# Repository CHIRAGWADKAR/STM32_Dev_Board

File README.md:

# STM32 PCB Design Project

## STM32F103C8T6 Dev Board (Custom PCB)

This repository contains the complete KiCad project files for a custom development board based on the **STM32F103C8T6** microcontroller, 
commonly used in embedded systems and ARM Cortex-M3 learning platforms.

Designed by: **Chirag Wadkar**  
Toolchain: **KiCad 5.1.15**

---

## 🔧 Features & Specifications

- **Microcontroller**: STM32F103C8T6 (ARM Cortex-M3, 72 MHz, 64 KB Flash, 20 KB RAM)
- **Voltage Regulation**: AMS1117-3.3 LDO with LED power indicator
- **Power Supply**: USB Micro-B (VBus) → 3.3V regulated
- **External Oscillator**:
  - 16 MHz crystal connected to PD0 (HSE_IN) & PD1 (HSE_OUT)
- **USB Interface**:
  - USB Micro-B connected to PA11 (D-) and PA12 (D+)
  - 1.5kΩ pull-up resistor on D+
- **Communication**:
  - UART: PB6 (TX), PB7 (RX)
  - I2C: PB10 (SCL), PB11 (SDA)

---

## 📷 Screenshots

### 🔌 Schematic View

### 💻 PCB Layout

### 🧱 3D Render

---

## 🔌 Powering & Programming

- **Power Input**: USB Micro-B (VBus 5V → Regulated to 3.3V)
- **Programming Methods**:
  - Via USB (DFU mode)
  - External SWD programmer via SWDIO/SWCLK pins.

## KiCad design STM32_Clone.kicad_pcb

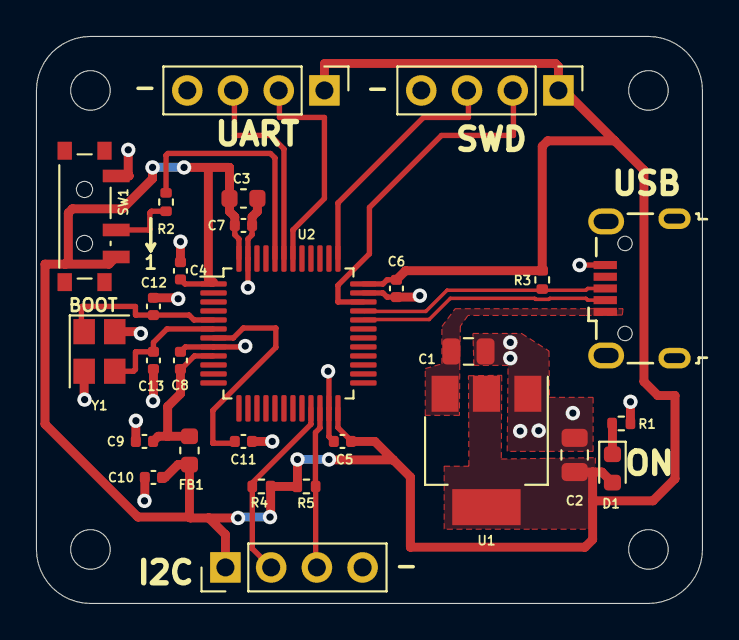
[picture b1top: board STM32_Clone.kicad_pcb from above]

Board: 2 copper layers, 37.0 x 31.5 mm, 32 parts (0 on the bottom side), 18 nets.

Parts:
C1, C2: 22u; C_0805_2012Metric
C3: 10u; C_0603_1608Metric
C4, C5, C6, C7, C11: 100n; C_0402_1005Metric
C8: 10n; C_0402_1005Metric
C9, C10: 1u; C_0402_1005Metric
C12, C13: 10p; C_0402_1005Metric
D1: RED; LED_0603_1608Metric
FB1: 120R; L_0603_1608Metric
H1, H2, H3, H4: MountingHole; MountingHole_2.2mm_M2
J1: USB_B_Micro; USB_Micro-B_Wuerth_629105150521
J2, J3, J4: Conn_01x04_Male; PinHeader_1x04_P2.54mm_Vertical
R1, R3, R4, R5: 1k5; R_0402_1005Metric
R2: 10k; R_0402_1005Metric
SW1: SW_SPDT; SW_SPDT_PCM12
U1: AMS1117-3.3; SOT-223-3_TabPin2
U2: STM32F103C8T6; LQFP-48_7x7mm_P0.5mm
Y1: 16MHz; Crystal_SMD_3225-4Pin_3.2x2.5mm

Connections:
+3.3VA: C8.1, C9.1, FB1.2, U2.9
+3V3: C2.1, C3.1, C4.1, C5.1, C6.1, C7.1, C10.1, D1.2, FB1.1, J2.1, J3.1, J4.1, R3.1, R4.1, R5.1, SW1.3, U1.2, U2.1, U2.24, U2.36, U2.48
/BOOT0: R2.1, U2.44
/HSE_IN: C12.1, U2.5, Y1.1
/HSE_OUT: C13.1, U2.6, Y1.3
/I2C2_SCL: J4.2, R4.2, U2.21
/I2C2_SDA: J4.3, R5.2, U2.22
/NRST: C11.1, U2.7
/PWR_LED_K: D1.1, R1.1
/SWCLK: J3.3, U2.37
/SWDIO: J3.2, U2.34
/SW_BOOT0: R2.2, SW1.2
/USART1_RX: J2.3, U2.43
/USART1_TX: J2.2, U2.42
/USB_D+: J1.3, R3.2, U2.33
/USB_D-: J1.2, U2.32
GND: C1.2, C2.2, C3.2, C4.2, C5.2, C6.2, C7.2, C8.2, C9.2, C10.2, C11.2, C12.2, C13.2, J1.5, J2.4, J3.4, J4.4, R1.2, SW1.1, U1.1, U2.8, U2.23, U2.35, U2.47, Y1.2, Y1.4
VBUS: C1.1, J1.1, U1.3

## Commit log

2025-06-21 Initial Commit - STM32 PCB
2025-06-21 added images, changed Readme file
2025-06-21 added gerber files
